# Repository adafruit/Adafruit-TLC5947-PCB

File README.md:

## Adafruit 24-Channel 12-bit PWM LED Driver - SPI Interface TLC5947 PCB
<a href="http://www.adafruit.com/products/1429"><br/>
Click here to purchase one from the Adafruit shop</a>

For all of you out there who want to control 24 channels of PWM, we salute you! We also would like you to check out this breakout board for the TLC5947 PWM driver chip. This chip can control 24 separate channels of 12-bit PWM output. Designed (and ideal) for LED control, this board is not good for driving servos. If you need to drive servos, we have a controller for that over here.

Only three "SPI" pins are required to send data (our Arduino library shows how to to use any digital microcontroller pins). Best of all, the design is completely chainable. As long as there's enough power for all the boards you can chain as many as you'd like, like a little trail of blue PCBs stretching out into the sunset. Each of the 24 output's is constant-current and open drain. You can drive multiple LEDs in series, with a V+ anode supply of up to 30V. If you want to drive something that requires a digital input, you must use a pullup resistor from the drive pin to your logic level to create the full waveform.

PCB files for Adafruit TLC5947 24-channel PWM Driver PCB. The format is EagleCAD schematic and board layout
- http://www.adafruit.com/products/1429

### License

Adafruit invests time and resources providing this open source design, please support Adafruit and open-source hardware by purchasing products from [Adafruit](https://www.adafruit.com)!

All text above must be included in any redistribution

Designed by Limor Fried/Ladyada for Adafruit Industries.
Creative Commons Attribution/Share-Alike, all text above must be included in any redistribution. 
See license.txt for additional information.

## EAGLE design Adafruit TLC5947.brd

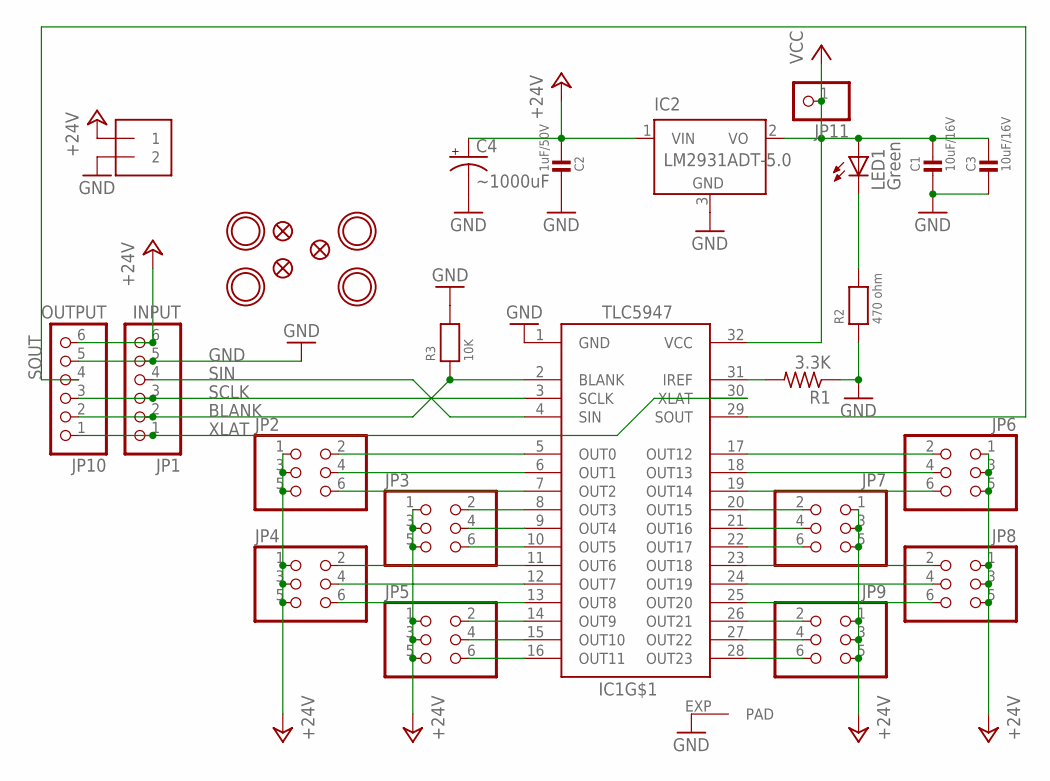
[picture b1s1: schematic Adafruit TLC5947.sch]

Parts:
C1, C3: 10uF/16V; 0805
C2: 1uF/50V; 0805
C4: ~1000uF; E3,5-8
FID1, FID2, FID3: FIDUCIAL""; FIDUCIAL_1MM
IC1: TLC5947-DAP; HTSSOP32DAP
IC2: LM2931ADT-5.0; TO252
J1: 1X2-3.5MM
JP1: INPUT; 1X06-CLEANBIG
JP2, JP3, JP4, JP5, JP6, JP7, JP8, JP9: HEADER-2X3; 2X03_ROUND_70MIL
JP10: OUTPUT; 1X06-CLEANBIG
JP11: PINHD-1X1CB; 1X01-CLEANBIG
LED1: Green; CHIP-LED0805
R1: 3.3K; 0805-THM
R2: 470 ohm; 0805
R3: 10K; 0805
U$1, U$2, U$3, U$4: MOUNTINGHOLE2.5; MOUNTINGHOLE_2.5_PLATED

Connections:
+24V: C2.1, C4.+, IC2.1 (VIN), J1.1, JP1.6, JP2.1, JP2.3, JP2.5, JP3.1, JP3.3, JP3.5, JP4.1, JP4.3, JP4.5, JP5.1, JP5.3, JP5.5, JP6.1, JP6.3, JP6.5, JP7.1, JP7.3, JP7.5, JP8.1, JP8.3, JP8.5, JP9.1, JP9.3, JP9.5, JP10.6
BLANK: IC1.2 (BLANK), JP1.2, JP10.2, R3.1
GND: C1.2, C2.2, C3.2, C4.-, IC1.1 (GND), IC1.EXP (PAD), IC2.3 (GND), J1.2, JP1.5, JP10.5, R1.1, R2.1, R3.2
unnamed: LED1.C, R2.2
unnamed: IC1.31 (IREF), R1.2
unnamed: IC1.5 (OUT0), JP2.2
unnamed: IC1.6 (OUT1), JP2.4
unnamed: IC1.7 (OUT2), JP2.6
unnamed: IC1.8 (OUT3), JP3.2
unnamed: IC1.9 (OUT4), JP3.4
unnamed: IC1.10 (OUT5), JP3.6
unnamed: IC1.11 (OUT6), JP4.2
unnamed: IC1.12 (OUT7), JP4.4
unnamed: IC1.13 (OUT8), JP4.6
unnamed: IC1.14 (OUT9), JP5.2
unnamed: IC1.15 (OUT10), JP5.4
unnamed: IC1.16 (OUT11), JP5.6
unnamed: IC1.26 (OUT21), JP9.2
unnamed: IC1.27 (OUT22), JP9.4
unnamed: IC1.28 (OUT23), JP9.6
unnamed: IC1.23 (OUT18), JP8.2
unnamed: IC1.24 (OUT19), JP8.4
unnamed: IC1.25 (OUT20), JP8.6
unnamed: IC1.20 (OUT15), JP7.2
unnamed: IC1.21 (OUT16), JP7.4
unnamed: IC1.22 (OUT17), JP7.6
unnamed: IC1.17 (OUT12), JP6.2
unnamed: IC1.18 (OUT13), JP6.4
unnamed: IC1.19 (OUT14), JP6.6
SCLK: IC1.3 (SCLK), JP1.3, JP10.3
SIN: IC1.4 (SIN), JP1.4
SOUT: IC1.29 (SOUT), JP10.4
VCC: C1.1, C3.1, IC1.32 (VCC), IC2.2 (VO), JP11.1, LED1.A
XLAT: IC1.30 (XLAT), JP1.1, JP10.1

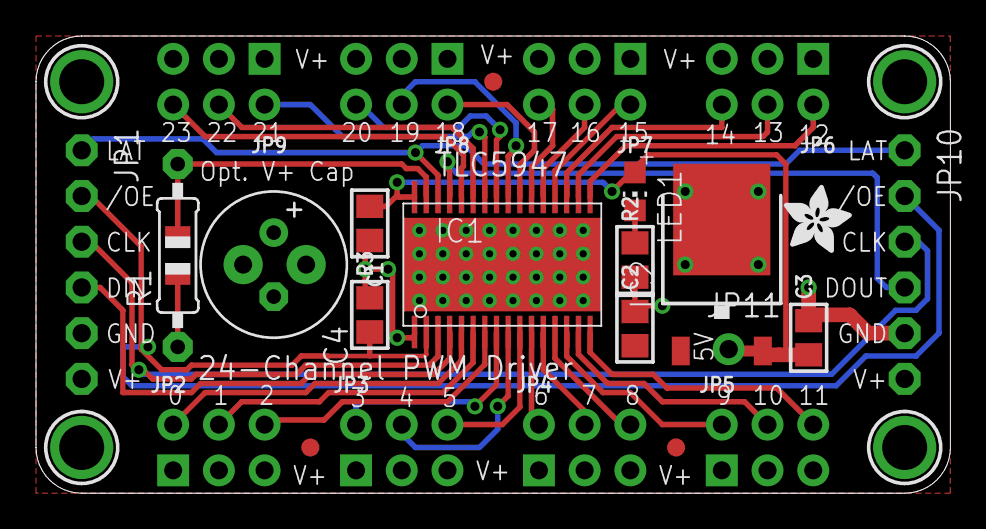
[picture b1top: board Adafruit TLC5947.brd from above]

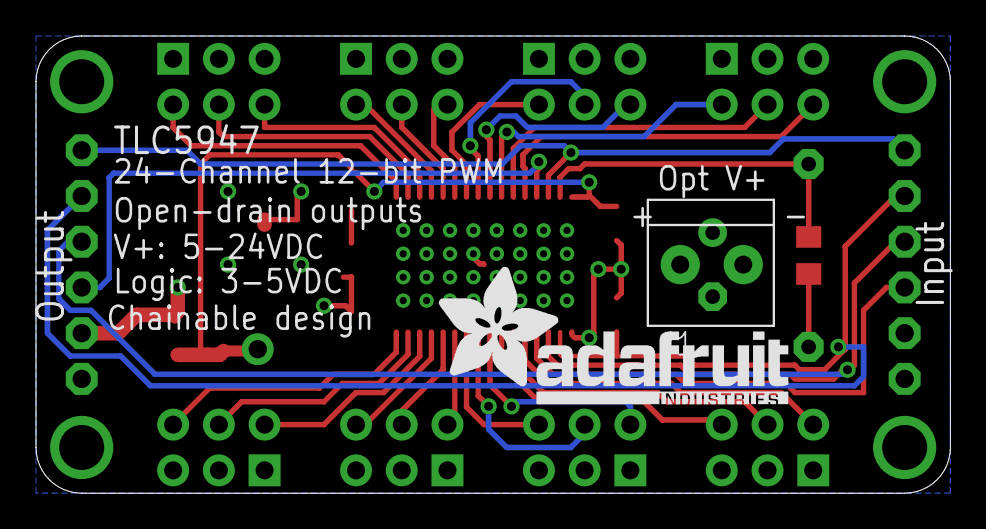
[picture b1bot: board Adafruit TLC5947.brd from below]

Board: 2 copper layers, 50.8 x 25.4 mm, 31 parts (2 on the bottom side), 34 nets.

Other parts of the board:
U$5: ADAFRUIT_TEXT_20MM
U$6: ADAFRUIT_3.5MM

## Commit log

2015-01-22 init
2016-02-08 Correct Product Link
    Product link in REAME.md should be "https://www.adafruit.com/products/1429", instead of "https://www.adafruit.com/products/1426".

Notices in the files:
parts and their libraries:
microbuilder: This work is placed in the public domain, and may be freely used for commercial and non-commercial work with the following conditions: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
